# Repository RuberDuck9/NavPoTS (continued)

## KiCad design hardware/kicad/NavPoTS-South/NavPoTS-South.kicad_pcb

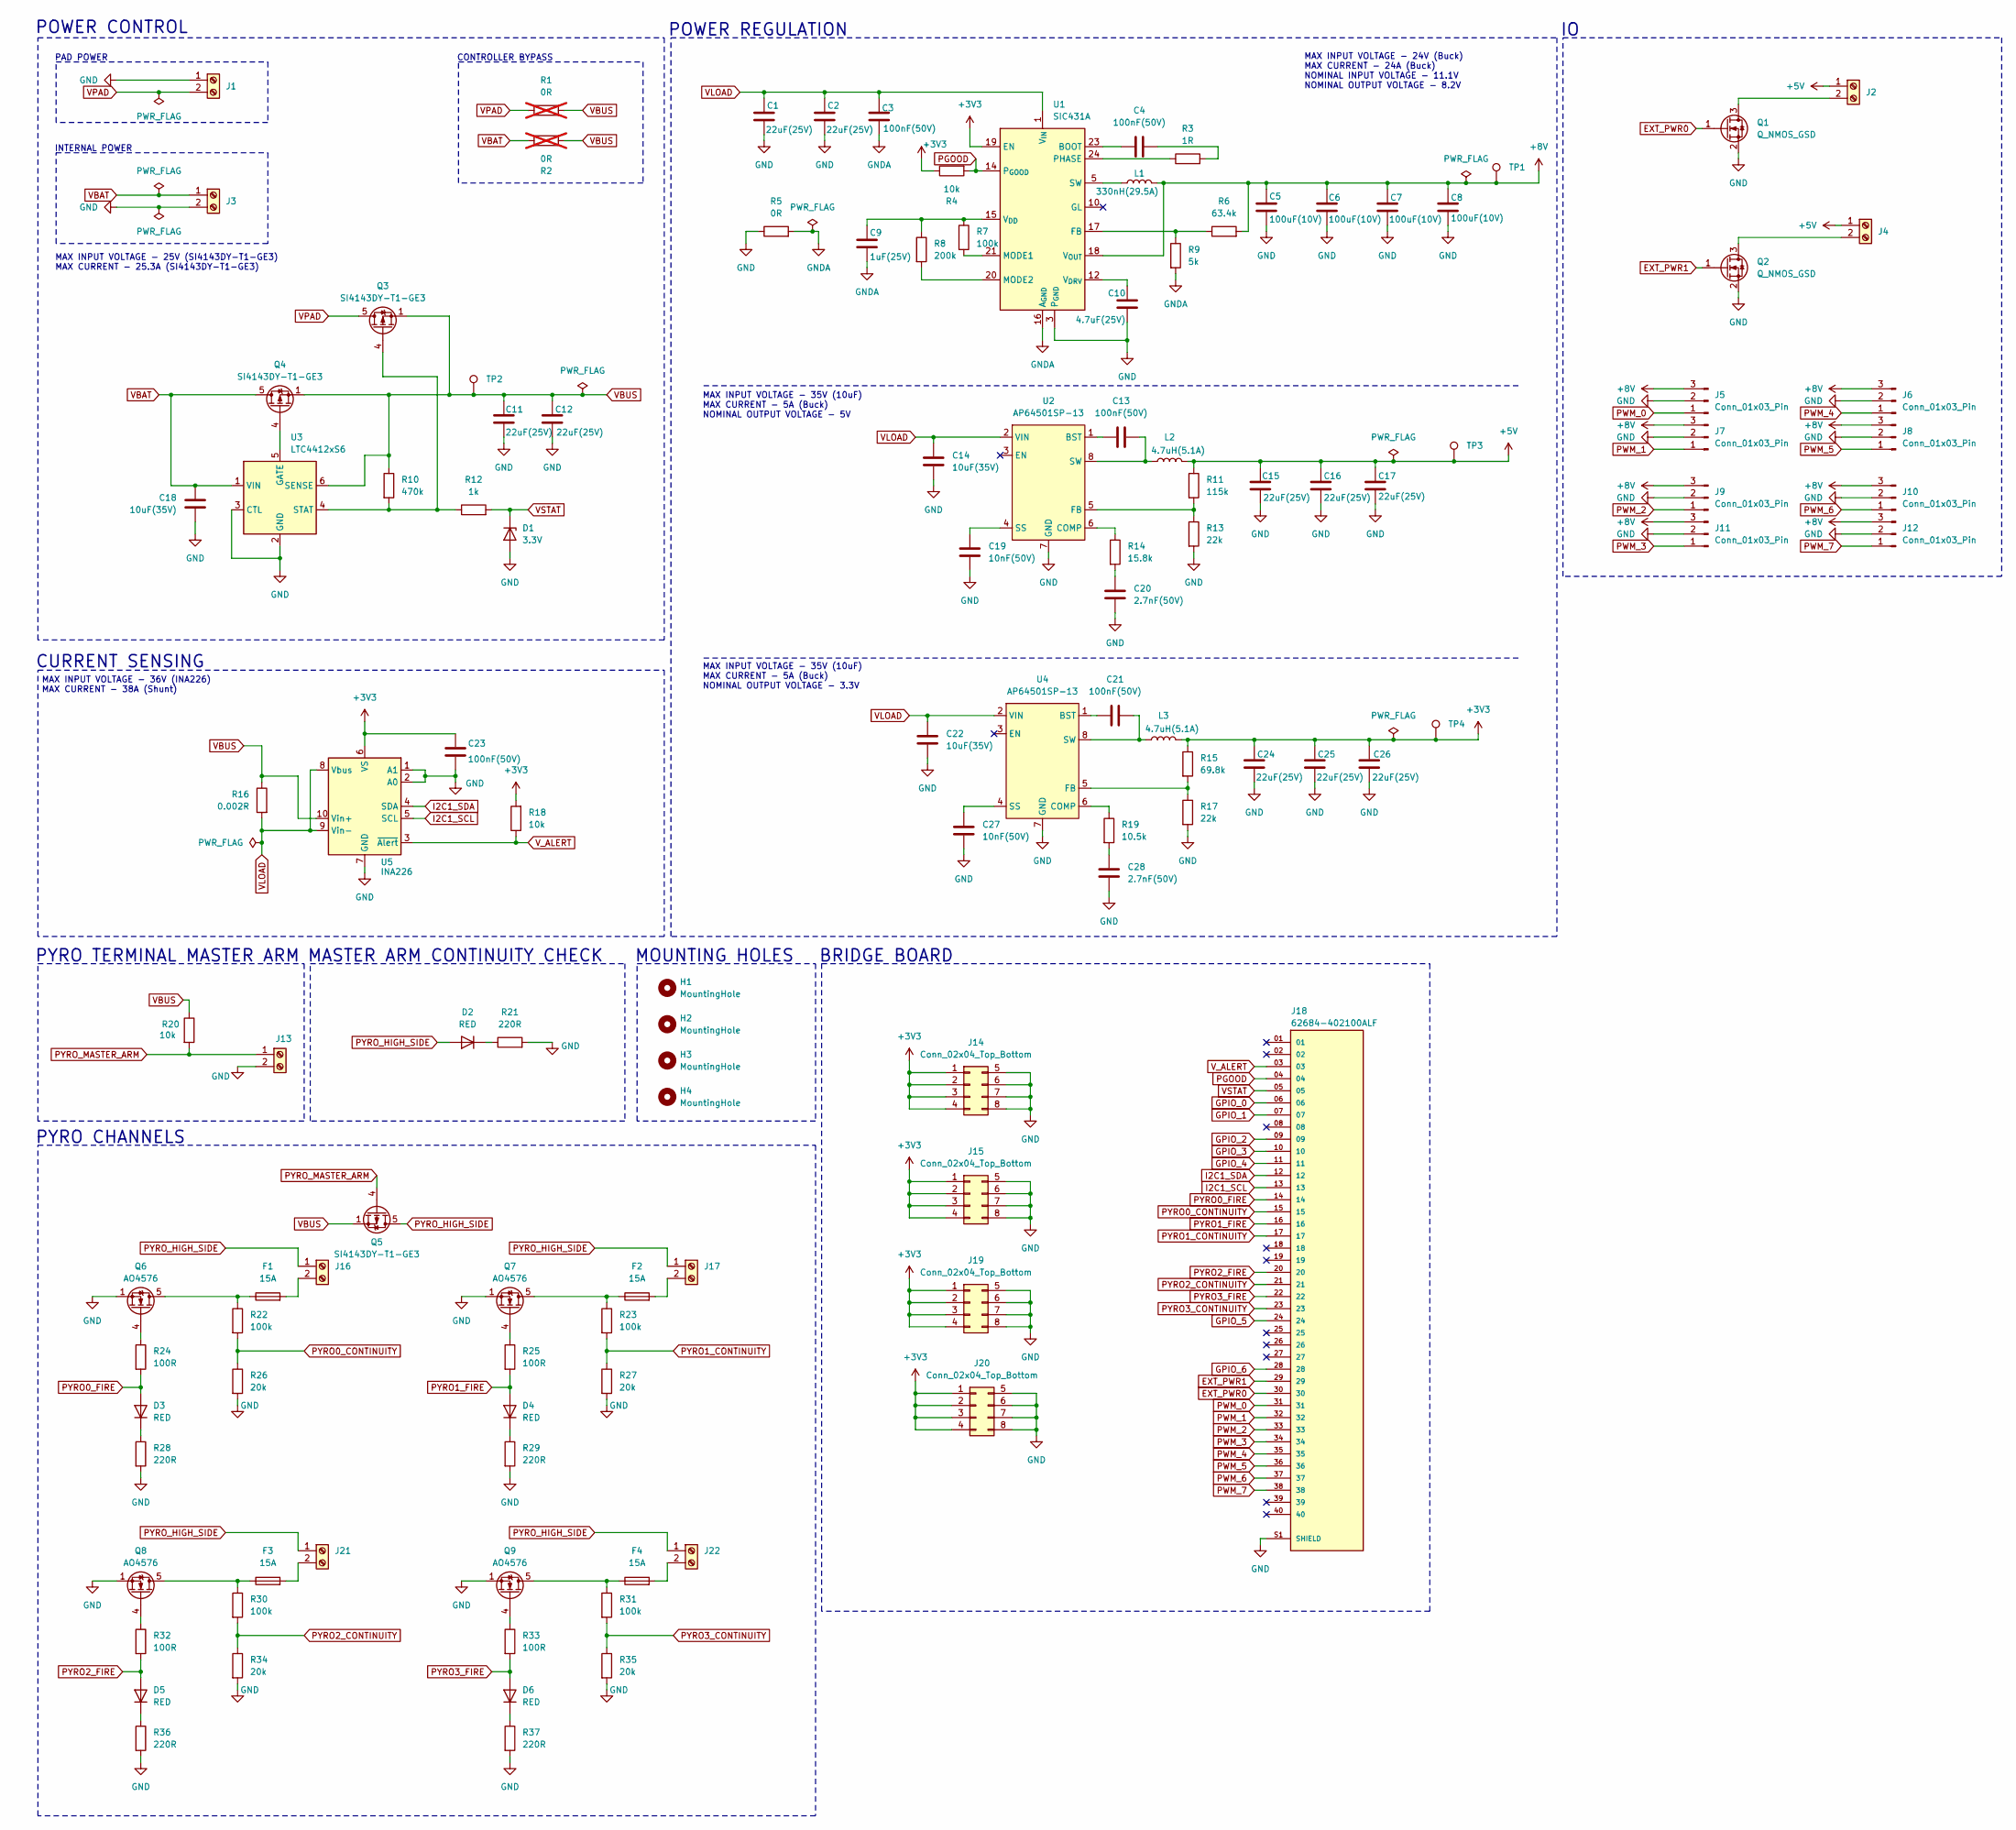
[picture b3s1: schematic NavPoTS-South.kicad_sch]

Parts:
C1, C2, C11, C12, C15, C16, C17, C24, C25, C26: 22uF(25V); C_0805_2012Metric_Pad1.18x1.45mm_HandSolder; MPN GRM21BR61E226ME44L
C3, C4, C13, C21, C23: 100nF(50V); C_0603_1608Metric_Pad1.08x0.95mm_HandSolder; MPN C0603C104K5RACTU
C5, C6, C7, C8: 100uF(10V); C_1206_3216Metric_Pad1.33x1.80mm_HandSolder; MPN C3216X5R1A107M160AC
C9: 1uF(25V); C_0603_1608Metric_Pad1.08x0.95mm_HandSolder; MPN CL10B105KA8NNNC
C10: 4.7uF(25V); C_0603_1608Metric_Pad1.08x0.95mm_HandSolder; MPN GRM188R61E475KE11D
C14, C18, C22: 10uF(35V); C_0603_1608Metric_Pad1.08x0.95mm_HandSolder; MPN GRM188R6YA106MA73D
C19, C27: 10nF(50V); C_0603_1608Metric_Pad1.08x0.95mm_HandSolder; MPN C0603C103K5RACTU
C20, C28: 2.7nF(50V); C_0603_1608Metric_Pad1.08x0.95mm_HandSolder; MPN GRM1885C1H272JA01D
D1: 3.3V; D_SOD-123; MPN MMSZ3V3T1G
D2, D3, D4, D5, D6: RED; LED_0603_1608Metric_Pad1.05x0.95mm_HandSolder; MPN LTST-C190KRKT
F1, F2, F3, F4: 15A; Fuse_1206_3216Metric_Pad1.42x1.75mm_HandSolder; MPN 0685H9150-01
H1, H2, H3, H4: MountingHole; MountingHole_3.2mm_M3
J1, J2, J3, J4, J13, J16, J17, J21, J22: Screw_Terminal_01x02; CONN_ED555_2DS; MPN ED555/2DS
J5, J6, J7, J8, J9, J10, J11, J12: Conn_01x03_Pin; PinHeader_1x03_P2.54mm_Vertical
J14, J15, J19, J20: Conn_02x04_Top_Bottom; PinSocket_2x04_P2.54mm_Vertical; MPN 61300821821
J18: 62684-402100ALF; Amphenol_62684-402100ALF; MPN 62684-402100ALF
L1: 330nH(29.5A); IND_IHLP-3232DZ_VIS; MPN IHLP3232DZERR33M01
L2, L3: 4.7uH(5.1A); L_Wuerth_MAPI-4030; MPN 74438357047
Q1, Q2: Q_NMOS_GSD; SOT-23-3; MPN AO3400A
Q3, Q4, Q5: SI4143DY-T1-GE3; SOIC-8_3.9x4.9mm_P1.27mm; MPN SI4143DY-T1-GE3
Q6, Q7, Q8, Q9: AO4576; SOIC-8_3.9x4.9mm_P1.27mm; MPN AO4576
R1, R2: 0R; R_0805_2012Metric_Pad1.20x1.40mm_HandSolder; MPN RC0805JR-070RL; not fitted
R3: 1R; R_0603_1608Metric_Pad0.98x0.95mm_HandSolder; MPN RC0603FR-071RL
R4, R18, R20: 10k; R_0603_1608Metric_Pad0.98x0.95mm_HandSolder; MPN RC0603FR-0710KL
R5: 0R; R_0603_1608Metric_Pad0.98x0.95mm_HandSolder; MPN RC0603JR-070RL
R6: 63.4k; R_0603_1608Metric_Pad0.98x0.95mm_HandSolder; MPN RMCF0603FT63K4
R7, R22, R23, R30, R31: 100k; R_0603_1608Metric_Pad0.98x0.95mm_HandSolder; MPN RC0603FR-07100KL
R8: 200k; R_0603_1608Metric_Pad0.98x0.95mm_HandSolder; MPN RC0603FR-07200KL
R9: 5k; R_0603_1608Metric_Pad0.98x0.95mm_HandSolder; MPN RT0603BRE075KL
R10: 470k; R_0603_1608Metric_Pad0.98x0.95mm_HandSolder; MPN RMCF0603FT470K
R11: 115k; R_0603_1608Metric_Pad0.98x0.95mm_HandSolder; MPN RC0603FR-07115KL
R12: 1k; R_0603_1608Metric_Pad0.98x0.95mm_HandSolder; MPN RC0603FR-071KL
R13, R17: 22k; R_0603_1608Metric_Pad0.98x0.95mm_HandSolder; MPN RC0603FR-0722KL
R14: 15.8k; R_0603_1608Metric_Pad0.98x0.95mm_HandSolder; MPN RC0603FR-0715K8L
R15: 69.8k; R_0603_1608Metric_Pad0.98x0.95mm_HandSolder; MPN RC0603FR-0769K8L
R16: 0.002R; R_2512_6332Metric_Pad1.40x3.35mm_HandSolder; MPN CRE2512-FZ-R002E-3
R19: 10.5k; R_0603_1608Metric_Pad0.98x0.95mm_HandSolder; MPN RC0603FR-0710K5L
R21, R28, R29, R36, R37: 220R; R_0603_1608Metric_Pad0.98x0.95mm_HandSolder; MPN RC0603FR-07220RL
R24, R25, R32, R33: 100R; R_0603_1608Metric_Pad0.98x0.95mm_HandSolder; MPN RC0603FR-07100RL
R26, R27, R34, R35: 20k; R_0603_1608Metric_Pad0.98x0.95mm_HandSolder; MPN RC0603FR-0720KL
TP1, TP2, TP3, TP4: TestPoint; TestPoint_Pad_D1.5mm
U1: SIC431A; Vishay_PowerPAK_MLP44-24L_ThermalVias; MPN SIC431AED-T1-GE3
U2, U4: AP64501SP-13; Diodes_SO-8EP; MPN AP64501SP-13
U3: LTC4412xS6; TSOT-23-6; MPN LTC4412IS6#TRPBF
U5: INA226; TSSOP-10_3x3mm_P0.5mm; MPN INA226AIDGSR

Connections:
+3V3: C23.1, C24.1, C25.1, C26.1, J14.1, J14.2, J14.3, J14.4, J15.1, J15.2, J15.3, J15.4, J19.1, J19.2, J19.3, J19.4, J20.1, J20.2, J20.3, J20.4, L3.2, R4.1, R15.1, R18.2, TP4.1 (1_1), U1.19 (EN), U5.6 (VS)
+5V: C15.1, C16.1, C17.1, J2.1, J4.1, L2.2, R11.1, TP3.1 (1_1)
+8V: C5.1, C6.1, C7.1, C8.1, J5.3, J6.3, J7.3, J8.3, J9.3, J10.3, J11.3, J12.3, L1.2, R6.2, TP1.1 (1_1), U1.18 (V_{OUT})
EXT_PWR0: J18.30, Q1.1 (G)
EXT_PWR1: J18.29, Q2.1 (G)
GND: C1.1, C2.2, C5.2, C6.2, C7.2, C8.2, C10.2, C11.1, C12.1, C14.2, C15.2, C16.2, C17.2, C18.2, C19.1, C20.2, C22.2, C23.2, C24.2, C25.2, C26.2, C27.1, C28.2, D1.2 (A), J1.1, J3.2, J5.2, J6.2, J7.2, J8.2, J9.2, J10.2, J11.2, J12.2, J13.2, J14.5, J14.6, J14.7, J14.8, J15.5, J15.6, J15.7, J15.8, J18.S1 (SHIELD), J18.S2 (SHIELD), J19.5, J19.6, J19.7, J19.8, J20.5, J20.6, J20.7, J20.8, Q1.2 (S), Q2.2 (S), Q6.1, Q6.2, Q6.3, Q7.1, Q7.2, Q7.3, Q8.1, Q8.2, Q8.3, Q9.1, Q9.2, Q9.3, R5.1, R13.2, R17.2, R21.2, R26.2, R27.2, R28.2, R29.2, R34.2, R35.2, R36.2, R37.2, U1.3 (P_{GND}), U1.4 (P_{GND}), U1.13 (P_{GND}), U1.27 (P_{GND}), U2.7 (GND), U2.9 (GND), U3.2 (GND), U3.3 (CTL), U4.7 (GND), U4.9 (GND), U5.1 (A1), U5.2 (A0), U5.7 (GND)
GNDA: C3.2, C9.2, R5.2, R9.2, U1.16 (A_{GND}), U1.25 (A_{GND})
GPIO_0: J18.06
GPIO_1: J18.07
GPIO_2: J18.09
GPIO_3: J18.10
GPIO_4: J18.11
GPIO_5: J18.24
GPIO_6: J18.28
I2C1_SCL: J18.13, U5.5 (SCL)
I2C1_SDA: J18.12, U5.4 (SDA)
unnamed: C4.2, R3.2
unnamed: C20.1, R14.2
unnamed: C28.1, R19.2
unnamed: D2.1 (K), R21.1
unnamed: D3.1 (K), R28.1
unnamed: D4.1 (K), R29.1
unnamed: D5.1 (K), R36.1
unnamed: D6.1 (K), R37.1
unnamed: F1.1, Q6.5, Q6.6, Q6.7, Q6.8, R22.1
unnamed: F2.1, Q7.5, Q7.6, Q7.7, Q7.8, R23.1
unnamed: F3.1, Q8.5, Q8.6, Q8.7, Q8.8, R30.1
unnamed: F4.1, Q9.5, Q9.6, Q9.7, Q9.8, R31.1
unnamed: J2.2, Q1.3 (D)
unnamed: J4.2, Q2.3 (D)
unnamed: F1.2, J16.2
unnamed: F2.2, J17.2
unnamed: F3.2, J21.2
unnamed: F4.2, J22.2
unnamed: L1.1, U1.5 (SW), U1.6 (SW), U1.7 (SW), U1.8 (SW), U1.9 (SW)
unnamed: Q6.4, R24.1
unnamed: Q7.4, R25.1
unnamed: Q8.4, R32.1
unnamed: Q9.4, R33.1
unnamed: C4.1, U1.23 (BOOT)
unnamed: R6.1, R9.1, U1.17 (FB)
unnamed: R7.2, U1.21 (MODE1)
unnamed: R8.2, U1.20 (MODE2)
unnamed: R3.1, U1.24 (PHASE)
unnamed: C9.1, R7.1, R8.1, U1.15 (V_{DD})
unnamed: C10.1, U1.12 (V_{DRV})
unnamed: C13.1, U2.1 (BST)
unnamed: R14.1, U2.6 (COMP)
unnamed: R11.2, R13.1, U2.5 (FB)
unnamed: C19.2, U2.4 (SS)
unnamed: C13.2, L2.1, U2.8 (SW)
unnamed: Q4.4, U3.5 (GATE)
unnamed: Q3.4, R10.2, R12.1, U3.4 (STAT)
unnamed: C21.1, U4.1 (BST)
unnamed: R19.1, U4.6 (COMP)
unnamed: R15.2, R17.1, U4.5 (FB)
unnamed: C27.2, U4.4 (SS)
unnamed: C21.2, L3.1, U4.8 (SW)
PGOOD: J18.04, R4.2, U1.14 (P_{GOOD})
PWM_0: J5.1, J18.31
PWM_1: J7.1, J18.32
PWM_2: J9.1, J18.33
PWM_3: J11.1, J18.34
PWM_4: J6.1, J18.35
PWM_5: J8.1, J18.36
PWM_6: J10.1, J18.37
PWM_7: J12.1, J18.38
PYRO0_CONTINUITY: J18.15, R22.2, R26.1
PYRO0_FIRE: D3.2 (A), J18.14, R24.2
PYRO1_CONTINUITY: J18.17, R23.2, R27.1
PYRO1_FIRE: D4.2 (A), J18.16, R25.2
PYRO2_CONTINUITY: J18.21, R30.2, R34.1
PYRO2_FIRE: D5.2 (A), J18.20, R32.2
PYRO3_CONTINUITY: J18.23, R31.2, R35.1
PYRO3_FIRE: D6.2 (A), J18.22, R33.2
PYRO_HIGH_SIDE: D2.2 (A), J16.1, J17.1, J21.1, J22.1, Q5.5, Q5.6, Q5.7, Q5.8
PYRO_MASTER_ARM: J13.1, Q5.4, R20.2
VBAT: C18.1, J3.1, Q4.5, Q4.6, Q4.7, Q4.8, R2.1, U3.1 (VIN)
VBUS: C11.2, C12.2, Q3.1, Q3.2, Q3.3, Q4.1, Q4.2, Q4.3, Q5.1, Q5.2, Q5.3, R1.2, R2.2, R10.1, R16.1, R20.1, TP2.1 (1_1), U3.6 (SENSE), U5.10 (Vin+)
VLOAD: C1.2, C2.1, C3.1, C14.1, C22.1, R16.2, U1.1 (V_{IN}), U1.2 (V_{IN}), U1.22 (V_{IN}), U1.26 (V_{IN}), U2.2 (VIN), U4.2 (VIN), U5.8 (Vbus), U5.9 (Vin-)
VPAD: J1.2, Q3.5, Q3.6, Q3.7, Q3.8, R1.1
VSTAT: D1.1 (K), J18.05, R12.2
V_ALERT: J18.03, R18.1, U5.3 (~Alert)

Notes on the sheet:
INTERNAL POWER
CURRENT SENSING
PAD POWER
PYRO TERMINAL MASTER ARM
POWER CONTROL
MOUNTING HOLES
BRIDGE BOARD
MAX INPUT VOLTAGE - 25V (SI4143DY-T1-GE3) MAX CURRENT - 25.3A (SI4143DY-T1-GE3)
MAX INPUT VOLTAGE - 24V (Buck) MAX CURRENT - 24A (Buck) NOMINAL INPUT VOLTAGE - 11.1V NOMINAL OUTPUT VOLTAGE - 8.2V
MAX INPUT VOLTAGE - 35V (10uF) MAX CURRENT - 5A (Buck) NOMINAL OUTPUT VOLTAGE - 5V
MAX INPUT VOLTAGE - 36V (INA226) MAX CURRENT - 38A (Shunt)
PYRO CHANNELS
MASTER ARM CONTINUITY CHECK
CONTROLLER BYPASS
POWER REGULATION
MAX INPUT VOLTAGE - 35V (10uF) MAX CURRENT - 5A (Buck) NOMINAL OUTPUT VOLTAGE - 3.3V

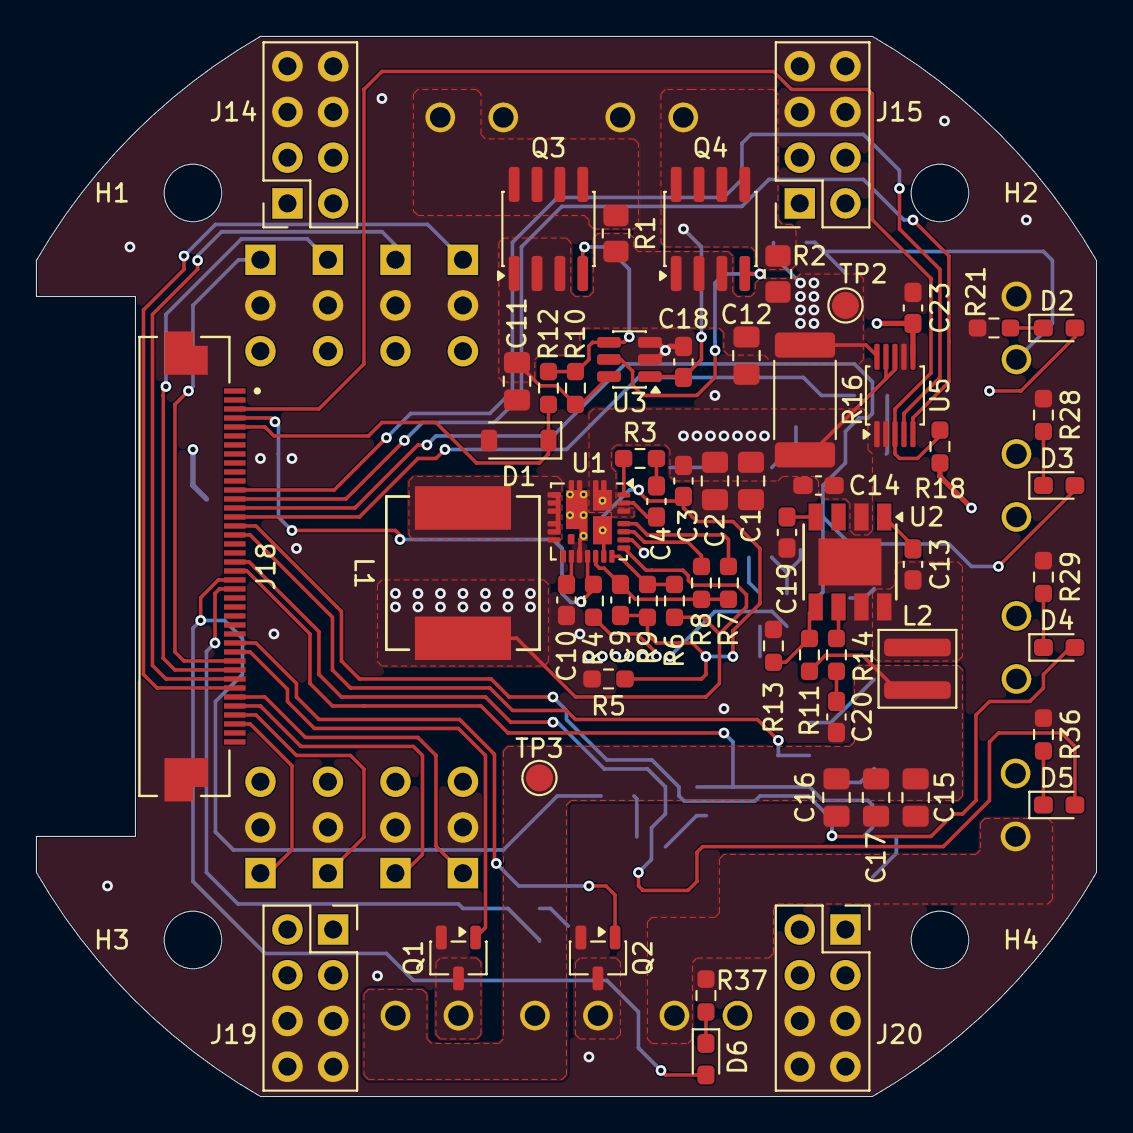
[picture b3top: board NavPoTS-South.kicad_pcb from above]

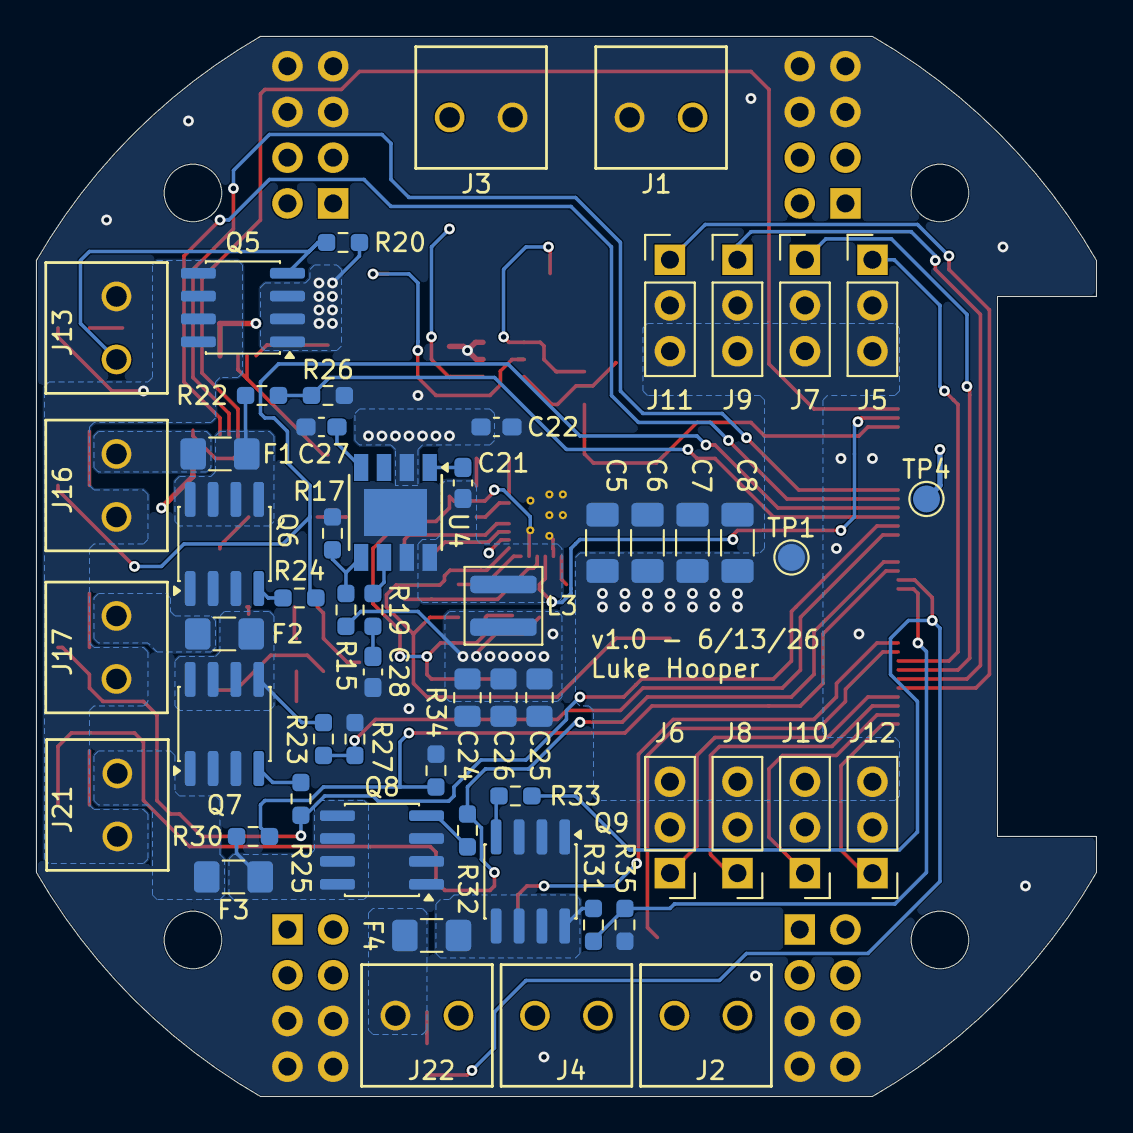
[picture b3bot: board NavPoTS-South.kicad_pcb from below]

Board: 4 copper layers, 58.9 x 58.9 mm, 122 parts (57 on the bottom side), 76 nets.

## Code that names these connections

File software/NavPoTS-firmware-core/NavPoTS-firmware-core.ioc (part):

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Mcu.Name=STM32H743ZITx
Mcu.Package=LQFP144
Mcu.UserName=STM32H743ZITx
PA0.Signal=S_TIM2_CH1_ETR
PA1.Signal=S_TIM2_CH2
PA11.Signal=USB_OTG_FS_DM
PA12.Signal=USB_OTG_FS_DP
PA13\ (JTMS/SWDIO).Signal=DEBUG_JTMS-SWDIO
PA14\ (JTCK/SWCLK).Signal=DEBUG_JTCK-SWCLK
PA2.Signal=S_TIM2_CH3
PA3.Signal=S_TIM2_CH4
PA6.Signal=S_TIM3_CH1
PA7.Signal=S_TIM3_CH2
PA8.Signal=GPIO_Output
PA9.Signal=USB_OTG_FS_VBUS
PB0.Signal=S_TIM3_CH3
PB1.Signal=S_TIM3_CH4
PB10.Mode=Asynchronous
PB10.Signal=USART3_TX
PB11.Mode=Asynchronous
PB11.Signal=USART3_RX
PB13.Mode=Full_Duplex_Master
PB13.Signal=SPI2_SCK
PB14.Mode=Full_Duplex_Master
PB14.Signal=SPI2_MISO
PB15.Mode=Full_Duplex_Master
PB15.Signal=SPI2_MOSI
PB3\ (JTDO/TRACESWO).Signal=DEBUG_JTDO-SWO
PC0.Signal=GPIO_Output
PC1.Signal=GPIO_Output
PC10.Mode=Full_Duplex_Master
PC10.Signal=SPI3_SCK
PC11.Mode=Full_Duplex_Master
PC11.Signal=SPI3_MISO
PC12.Mode=Full_Duplex_Master
PC12.Signal=SPI3_MOSI
PC13.Signal=GPIO_Output
PC14-OSC32_IN\ (OSC32_IN).Signal=GPIO_Output
PC15-OSC32_OUT\ (OSC32_OUT).Signal=GPIO_Output
PC2_C.Signal=GPIO_Output
PC6.Signal=GPIO_Output
PC7.Signal=GPIO_Output
PC8.Signal=GPIO_Output
PC9.Signal=GPIO_Output
PD0.Signal=GPIO_Output
PD1.Signal=GPIO_Output
PD10.Signal=GPIO_Output
PD11.Signal=GPIO_Output
PD12.Signal=GPIO_Output
PD13.Signal=GPIO_Output
PD14.Signal=GPIO_Output
PD15.Signal=GPIO_Output
PD2.Signal=GPIO_Output
PD3.Signal=GPIO_Output
PD4.Signal=GPIO_Output
PD8.Signal=GPIO_Output
PD9.Signal=GPIO_Output
PE14.Signal=GPIO_Output
PE15.Signal=GPIO_Output
PE2.Signal=GPIO_Input
PE3.Signal=GPIO_Input
PE4.Signal=GPIO_Input
PE5.Signal=GPIO_Output
PE6.Signal=GPIO_Output
PE7.Mode=Asynchronous
PE7.Signal=UART7_RX
PE8.Mode=Asynchronous
PE8.Signal=UART7_TX
PF0.Mode=I2C
PF0.Signal=I2C2_SDA
PF1.Mode=I2C
PF1.Signal=I2C2_SCL
PF10.Signal=GPIO_Output
PF14.Mode=I2C
PF14.Signal=I2C4_SCL
PF15.Mode=I2C
PF15.Signal=I2C4_SDA
PF2.Signal=GPIO_Output
PF3.Mode=IN5-Single-Ended
PF3.Signal=ADC3_INP5
PF4.Signal=GPIO_Output
PF5.Mode=IN4-Single-Ended
PF5.Signal=ADC3_INP4
PF6.Signal=GPIO_Output
PF7.Mode=IN3-Single-Ended
PF7.Signal=ADC3_INP3
PF8.Signal=GPIO_Output
PF9.Mode=IN2-Single-Ended
PF9.Signal=ADC3_INP2
PG2.Signal=GPIO_Output
PG3.Signal=GPIO_Output
PG4.Signal=GPIO_Output
PG5.Signal=GPIO_Output
PG6.Signal=GPIO_Output
PH0-OSC_IN\ (PH0).Mode=HSE-External-Clock-Source
PH0-OSC_IN\ (PH0).Signal=RCC_OSC_IN
RCC.SYSCLKFreq_VALUE=475000000
RCC.SYSCLKSource=RCC_SYSCLKSOURCE_PLLCLK
board=custom

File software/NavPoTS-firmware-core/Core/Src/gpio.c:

/* USER CODE BEGIN Header */
/**
  ******************************************************************************
  * @file    gpio.c
  * @brief   This file provides code for the configuration
  *          of all used GPIO pins.
  ******************************************************************************
  * @attention
  *
  * Copyright (c) 2026 STMicroelectronics.
  * All rights reserved.
  *
  * This software is licensed under terms that can be found in the LICENSE file
  * in the root directory of this software component.
  * If no LICENSE file comes with this software, it is provided AS-IS.
  *
  ******************************************************************************
  */
/* USER CODE END Header */

/* Includes ------------------------------------------------------------------*/
#include "gpio.h"

/* USER CODE BEGIN 0 */

/* USER CODE END 0 */

/*----------------------------------------------------------------------------*/
/* Configure GPIO                                                             */
/*----------------------------------------------------------------------------*/
/* USER CODE BEGIN 1 */

/* USER CODE END 1 */

/** Configure pins
     PH0-OSC_IN (PH0)   ------> RCC_OSC_IN
     PA9   ------> USB_OTG_FS_VBUS
     PA11   ------> USB_OTG_FS_DM
     PA12   ------> USB_OTG_FS_DP
     PA13 (JTMS/SWDIO)   ------> DEBUG_JTMS-SWDIO
     PA14 (JTCK/SWCLK)   ------> DEBUG_JTCK-SWCLK
     PB3 (JTDO/TRACESWO)   ------> DEBUG_JTDO-SWO
*/
void MX_GPIO_Init(void)
{

  GPIO_InitTypeDef GPIO_InitStruct = {0};

  /* GPIO Ports Clock Enable */
  __HAL_RCC_GPIOE_CLK_ENABLE();
  __HAL_RCC_GPIOC_CLK_ENABLE();
  __HAL_RCC_GPIOF_CLK_ENABLE();
  __HAL_RCC_GPIOH_CLK_ENABLE();
  __HAL_RCC_GPIOA_CLK_ENABLE();
  __HAL_RCC_GPIOB_CLK_ENABLE();
  __HAL_RCC_GPIOG_CLK_ENABLE();
  __HAL_RCC_GPIOD_CLK_ENABLE();

  /*Configure GPIO pin Output Level */
  HAL_GPIO_WritePin(GPIOE, GPIO_PIN_5|GPIO_PIN_6|GPIO_PIN_14|GPIO_PIN_15, GPIO_PIN_RESET);

  /*Configure GPIO pin Output Level */
  HAL_GPIO_WritePin(GPIOC, GPIO_PIN_13|GPIO_PIN_14|GPIO_PIN_15|GPIO_PIN_0
                          |GPIO_PIN_1|GPIO_PIN_2|GPIO_PIN_6|GPIO_PIN_7
                          |GPIO_PIN_8|GPIO_PIN_9, GPIO_PIN_RESET);

  /*Configure GPIO pin Output Level */
  HAL_GPIO_WritePin(GPIOF, GPIO_PIN_2|GPIO_PIN_4|GPIO_PIN_6|GPIO_PIN_8
                          |GPIO_PIN_10, GPIO_PIN_RESET);

  /*Configure GPIO pin Output Level */
  HAL_GPIO_WritePin(GPIOD, GPIO_PIN_8|GPIO_PIN_9|GPIO_PIN_10|GPIO_PIN_11
                          |GPIO_PIN_12|GPIO_PIN_13|GPIO_PIN_14|GPIO_PIN_15
                          |GPIO_PIN_0|GPIO_PIN_1|GPIO_PIN_2|GPIO_PIN_3
                          |GPIO_PIN_4, GPIO_PIN_RESET);

  /*Configure GPIO pin Output Level */
  HAL_GPIO_WritePin(GPIOG, GPIO_PIN_2|GPIO_PIN_3|GPIO_PIN_4|GPIO_PIN_5
                          |GPIO_PIN_6, GPIO_PIN_RESET);

  /*Configure GPIO pin Output Level */
  HAL_GPIO_WritePin(GPIOA, GPIO_PIN_8, GPIO_PIN_RESET);

  /*Configure GPIO pins : PE2 PE3 PE4 */
  GPIO_InitStruct.Pin = GPIO_PIN_2|GPIO_PIN_3|GPIO_PIN_4;
  GPIO_InitStruct.Mode = GPIO_MODE_INPUT;
  GPIO_InitStruct.Pull = GPIO_NOPULL;
  HAL_GPIO_Init(GPIOE, &GPIO_InitStruct);

  /*Configure GPIO pins : PE5 PE6 PE14 PE15 */
  GPIO_InitStruct.Pin = GPIO_PIN_5|GPIO_PIN_6|GPIO_PIN_14|GPIO_PIN_15;
  GPIO_InitStruct.Mode = GPIO_MODE_OUTPUT_PP;
  GPIO_InitStruct.Pull = GPIO_NOPULL;
  GPIO_InitStruct.Speed = GPIO_SPEED_FREQ_LOW;
  HAL_GPIO_Init(GPIOE, &GPIO_InitStruct);

  /*Configure GPIO pins : PC13 PC14 PC15 PC0
                           PC1 PC2 PC6 PC7
                           PC8 PC9 */
  GPIO_InitStruct.Pin = GPIO_PIN_13|GPIO_PIN_14|GPIO_PIN_15|GPIO_PIN_0
                          |GPIO_PIN_1|GPIO_PIN_2|GPIO_PIN_6|GPIO_PIN_7
                          |GPIO_PIN_8|GPIO_PIN_9;
  GPIO_InitStruct.Mode = GPIO_MODE_OUTPUT_PP;
  GPIO_InitStruct.Pull = GPIO_NOPULL;
  GPIO_InitStruct.Speed = GPIO_SPEED_FREQ_LOW;
  HAL_GPIO_Init(GPIOC, &GPIO_InitStruct);

  /*Configure GPIO pins : PF2 PF4 PF6 PF8
                           PF10 */
  GPIO_InitStruct.Pin = GPIO_PIN_2|GPIO_PIN_4|GPIO_PIN_6|GPIO_PIN_8
                          |GPIO_PIN_10;
  GPIO_InitStruct.Mode = GPIO_MODE_OUTPUT_PP;
  GPIO_InitStruct.Pull = GPIO_NOPULL;
  GPIO_InitStruct.Speed = GPIO_SPEED_FREQ_LOW;
  HAL_GPIO_Init(GPIOF, &GPIO_InitStruct);

  /*Configure GPIO pin : PH1 */
  GPIO_InitStruct.Pin = GPIO_PIN_1;
  GPIO_InitStruct.Mode = GPIO_MODE_ANALOG;
  GPIO_InitStruct.Pull = GPIO_NOPULL;
  HAL_GPIO_Init(GPIOH, &GPIO_InitStruct);

  /*Configure GPIO pins : PC3 PC4 PC5 */
  GPIO_InitStruct.Pin = GPIO_PIN_3|GPIO_PIN_4|GPIO_PIN_5;
  GPIO_InitStruct.Mode = GPIO_MODE_ANALOG;
  GPIO_InitStruct.Pull = GPIO_NOPULL;
  HAL_GPIO_Init(GPIOC, &GPIO_InitStruct);

  /*Configure GPIO pins : PA4 PA5 PA10 PA15 */
  GPIO_InitStruct.Pin = GPIO_PIN_4|GPIO_PIN_5|GPIO_PIN_10|GPIO_PIN_15;
  GPIO_InitStruct.Mode = GPIO_MODE_ANALOG;
  GPIO_InitStruct.Pull = GPIO_NOPULL;
  HAL_GPIO_Init(GPIOA, &GPIO_InitStruct);

  /*Configure GPIO pins : PB2 PB12 PB4 PB5
                           PB6 PB7 PB8 PB9 */
  GPIO_InitStruct.Pin = GPIO_PIN_2|GPIO_PIN_12|GPIO_PIN_4|GPIO_PIN_5
                          |GPIO_PIN_6|GPIO_PIN_7|GPIO_PIN_8|GPIO_PIN_9;
  GPIO_InitStruct.Mode = GPIO_MODE_ANALOG;
  GPIO_InitStruct.Pull = GPIO_NOPULL;
  HAL_GPIO_Init(GPIOB, &GPIO_InitStruct);

  /*Configure GPIO pins : PF11 PF12 PF13 */
  GPIO_InitStruct.Pin = GPIO_PIN_11|GPIO_PIN_12|GPIO_PIN_13;
  GPIO_InitStruct.Mode = GPIO_MODE_ANALOG;
  GPIO_InitStruct.Pull = GPIO_NOPULL;
  HAL_GPIO_Init(GPIOF, &GPIO_InitStruct);

  /*Configure GPIO pins : PG0 PG1 PG7 PG8
                           PG9 PG10 PG11 PG12
                           PG13 PG14 PG15 */
  GPIO_InitStruct.Pin = GPIO_PIN_0|GPIO_PIN_1|GPIO_PIN_7|GPIO_PIN_8
                          |GPIO_PIN_9|GPIO_PIN_10|GPIO_PIN_11|GPIO_PIN_12
                          |GPIO_PIN_13|GPIO_PIN_14|GPIO_PIN_15;
  GPIO_InitStruct.Mode = GPIO_MODE_ANALOG;
  GPIO_InitStruct.Pull = GPIO_NOPULL;
  HAL_GPIO_Init(GPIOG, &GPIO_InitStruct);

  /*Configure GPIO pins : PE9 PE10 PE11 PE12
                           PE13 PE0 PE1 */
  GPIO_InitStruct.Pin = GPIO_PIN_9|GPIO_PIN_10|GPIO_PIN_11|GPIO_PIN_12
                          |GPIO_PIN_13|GPIO_PIN_0|GPIO_PIN_1;
  GPIO_InitStruct.Mode = GPIO_MODE_ANALOG;
  GPIO_InitStruct.Pull = GPIO_NOPULL;
  HAL_GPIO_Init(GPIOE, &GPIO_InitStruct);

  /*Configure GPIO pins : PD8 PD9 PD10 PD11
                           PD12 PD13 PD14 PD15
                           PD0 PD1 PD2 PD3
                           PD4 */
  GPIO_InitStruct.Pin = GPIO_PIN_8|GPIO_PIN_9|GPIO_PIN_10|GPIO_PIN_11
                          |GPIO_PIN_12|GPIO_PIN_13|GPIO_PIN_14|GPIO_PIN_15
                          |GPIO_PIN_0|GPIO_PIN_1|GPIO_PIN_2|GPIO_PIN_3
                          |GPIO_PIN_4;
  GPIO_InitStruct.Mode = GPIO_MODE_OUTPUT_PP;
  GPIO_InitStruct.Pull = GPIO_NOPULL;
  GPIO_InitStruct.Speed = GPIO_SPEED_FREQ_LOW;
  HAL_GPIO_Init(GPIOD, &GPIO_InitStruct);

  /*Configure GPIO pins : PG2 PG3 PG4 PG5
                           PG6 */
  GPIO_InitStruct.Pin = GPIO_PIN_2|GPIO_PIN_3|GPIO_PIN_4|GPIO_PIN_5
                          |GPIO_PIN_6;
  GPIO_InitStruct.Mode = GPIO_MODE_OUTPUT_PP;
  GPIO_InitStruct.Pull = GPIO_NOPULL;
  GPIO_InitStruct.Speed = GPIO_SPEED_FREQ_LOW;
  HAL_GPIO_Init(GPIOG, &GPIO_InitStruct);

  /*Configure GPIO pin : PA8 */
  GPIO_InitStruct.Pin = GPIO_PIN_8;
  GPIO_InitStruct.Mode = GPIO_MODE_OUTPUT_PP;
  GPIO_InitStruct.Pull = GPIO_NOPULL;
  GPIO_InitStruct.Speed = GPIO_SPEED_FREQ_LOW;
  HAL_GPIO_Init(GPIOA, &GPIO_InitStruct);

  /*Configure GPIO pins : PA11 PA12 */
  GPIO_InitStruct.Pin = GPIO_PIN_11|GPIO_PIN_12;
  GPIO_InitStruct.Mode = GPIO_MODE_AF_PP;
  GPIO_InitStruct.Pull = GPIO_NOPULL;
  GPIO_InitStruct.Speed = GPIO_SPEED_FREQ_LOW;
  GPIO_InitStruct.Alternate = GPIO_AF10_OTG1_FS;
  HAL_GPIO_Init(GPIOA, &GPIO_InitStruct);

  /*Configure GPIO pins : PD5 PD6 PD7 */
  GPIO_InitStruct.Pin = GPIO_PIN_5|GPIO_PIN_6|GPIO_PIN_7;
  GPIO_InitStruct.Mode = GPIO_MODE_ANALOG;
  GPIO_InitStruct.Pull = GPIO_NOPULL;
  HAL_GPIO_Init(GPIOD, &GPIO_InitStruct);

  /*AnalogSwitch Config */
  HAL_SYSCFG_AnalogSwitchConfig(SYSCFG_SWITCH_PC2, SYSCFG_SWITCH_PC2_CLOSE);

}

/* USER CODE BEGIN 2 */

/* USER CODE END 2 */

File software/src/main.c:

/*
 * The following is a list of a the most important hardware connections in the version 1.0 of this project's pcb
 *
 * DEBUG_0 - PE15
 * DEBUG_1 - PE14
 * DEBUG_2 - PG3
 * DEBUG_3 - PG4
 * DEBUG_4 - PG5
 * DEBUG_5 - PG6
 *
 * SPI3_SCK - PC10
 * SPI3_MISO - PC11
 * SPI3_MOSI - PC12
 * SPI3_CS0 - PD0 - MS5611 Barometer
 * SPI3_CS1 - PD1 - ASM330LHHXTR IMU
 * SPI3_CS2 - PD3 - H3LIS331DLTR ACCEL
 * SPI3_CS3 - PD4 - MMC5983MA MAG
 * 
 * USART3_TX - PB10
 * USART3_RX - PB11
 *
 * UART7_RX - PE7
 * UART7_TX - PE8
 *
 * I2C4_SCL - PF14
 * I2C4_SDA - PF15
 *
 */

// libopencm3 includes
#include <libopencm3/stm32/gpio.h>

// local header includes
#include "gpio.h"
#include "usart.h"
#include "clock.h"
#include "delay.h"
#include "spi.h"

// port definitions
#define SPI3_SCK PC10

int main(void){

	//configure_system_clock();
	configure_systick();

	usart_init(RCC_GPIOB, RCC_USART3, GPIOB, GPIO11, GPIO10, USART3, 9600, USART_MODE_TX);

	spi_init(RCC_GPIOC, GPIOC, GPIO10, GPIO11, GPIO12, SPI3, SPI_CR1_BAUDRATE_FPCLK_DIV_32, SPI_CR1_CPOL_CLK_TO_0_WHEN_IDLE, SPI_CR1_CPHA_CLK_TRANSITION_2, SPI_CR1_MSBFIRST, SPI_CR2_DS_8BIT);
	volatile uint8_t chip_id = 0;
	
	while (1){
		usart_println(USART3, "Hello World!");

		set_pin(RCC_GPIOE, GPIOE, GPIO15);
		delay(200);

		clear_pin(RCC_GPIOE, GPIOE, GPIO15);
		delay(200);

		chip_id = spi_read_8(SPI3, RCC_GPIOD, GPIOD, GPIO1, 0x80);
	}

	return 0;
}
